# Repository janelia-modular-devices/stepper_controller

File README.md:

# stepper_controller

Authors:

    Peter Polidoro <polidorop@janelia.hhmi.org>

License:

    BSD

## More Detailed Help on Installation and Usage

[modular-devices](https://github.com/janelia-modular-devices/modular-devices)

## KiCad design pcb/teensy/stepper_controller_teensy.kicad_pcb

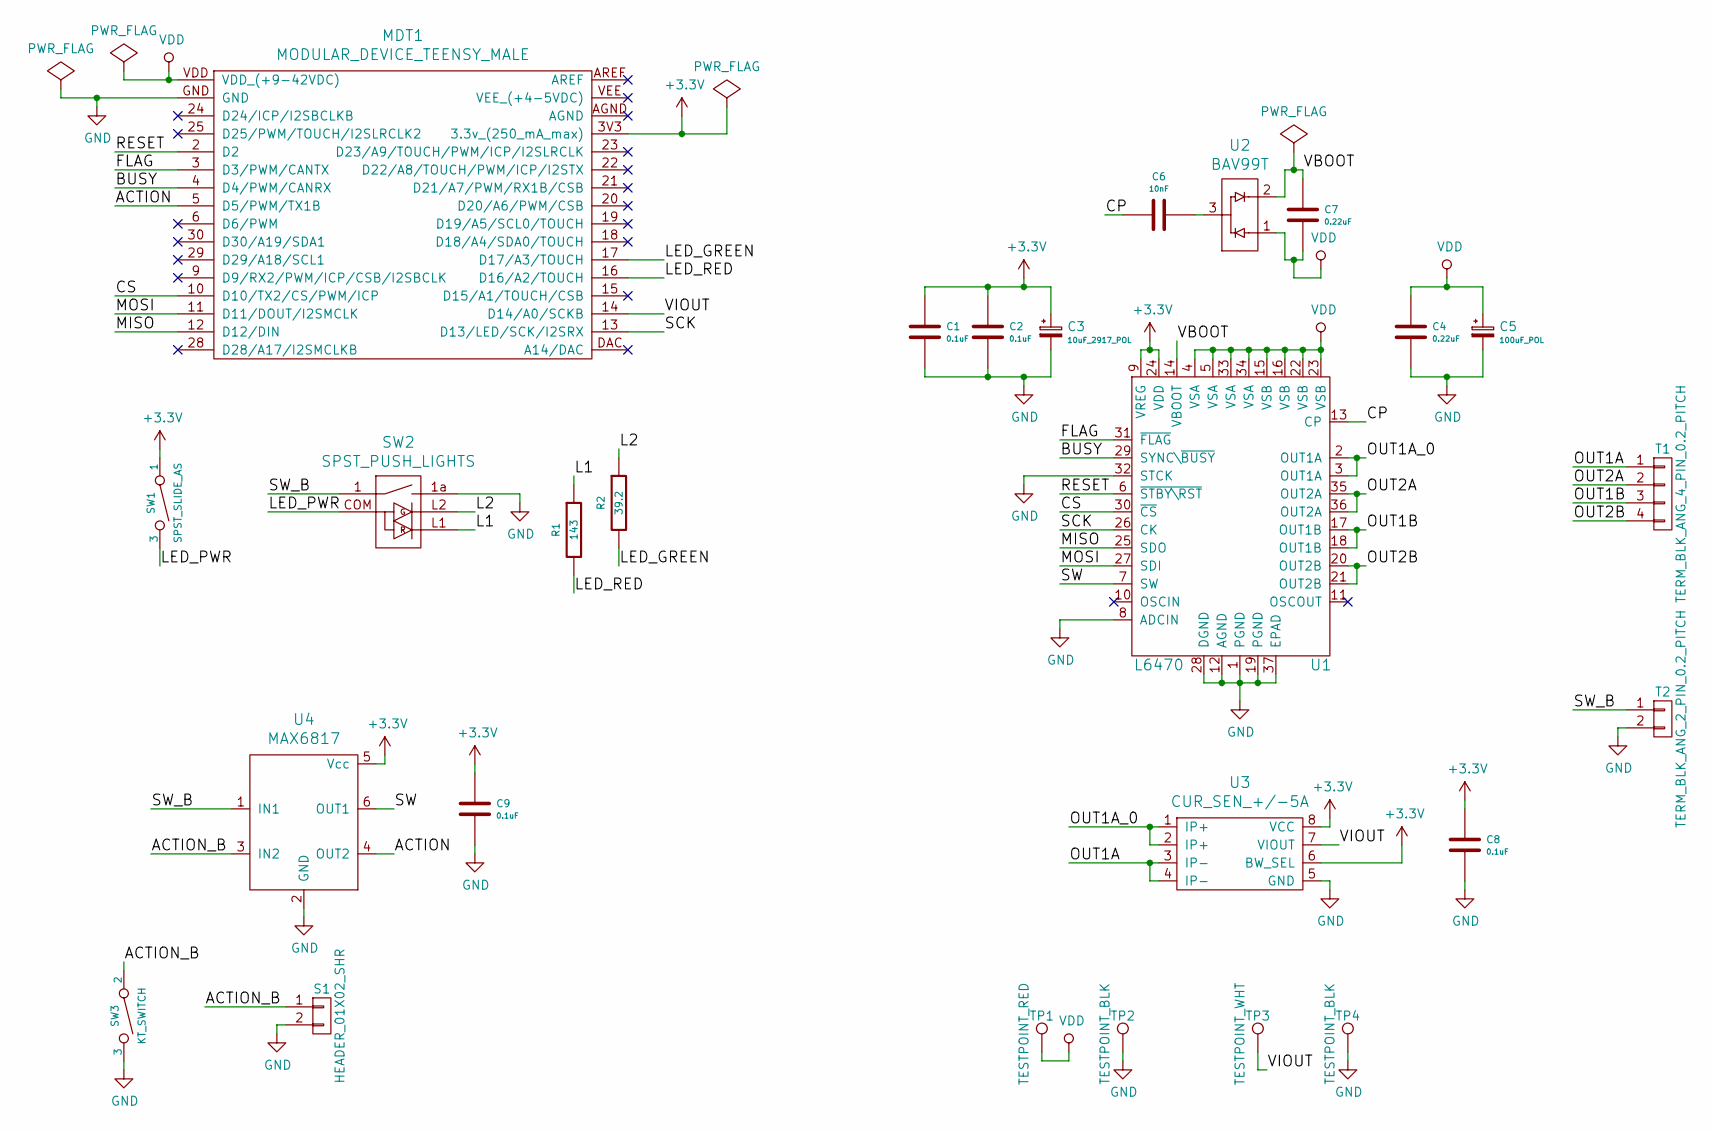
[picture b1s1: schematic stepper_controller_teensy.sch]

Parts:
C1, C2, C8, C9: 0.1uF; SM1210; PartNumber 478-3586-1-ND
C3: 10uF_2917_POL; SM2917_POL; PartNumber 399-8527-1-ND
C4, C7: 0.22uF; SM1210; PartNumber 399-11615-1-ND
C5: 100uF_POL; C_ELEC_12.5; PartNumber 565-2511-1-ND
C6: 10nF; SM1210; PartNumber 399-11960-1-ND
MDT1: MODULAR_DEVICE_TEENSY_MALE; PartNumber S1011E-16-ND
R1: 143; SM1210; PartNumber P143AACT-ND
R2: 39.2; SM1210; PartNumber P39.2AACT-ND
S1: HEADER_01X02_SHR; Header_Shrouded_2_Pin; PartNumber WM4800-ND
SW1: SPST_SLIDE_AS; PartNumber 360-2610-ND
SW2: SPST_PUSH_LIGHTS; KP_SWITCH; PartNumber 360-2461-ND
SW3: KT_SWITCH; PartNumber CKN1860CT-ND
T1: TERM_BLK_ANG_4_PIN_0.2_PITCH; PartNumber A98350-ND
T2: TERM_BLK_ANG_2_PIN_0.2_PITCH; PartNumber A98348-ND
TP1: TESTPOINT_RED; TESTPOINT_THRU; PartNumber 36-5010-ND
TP2, TP4: TESTPOINT_BLK; TESTPOINT_THRU; PartNumber 36-5011-ND
TP3: TESTPOINT_WHT; TESTPOINT_THRU; PartNumber 36-5012-ND
U1: L6470; POWERSO-36; PartNumber 497-16432-1-ND
U2: BAV99T; SOT-523; PartNumber BAV99TCT-ND
U3: CUR_SEN_+/-5A; SOIC_8_LC; PartNumber 620-1634-1-ND
U4: MAX6817; PartNumber MAX6817EUT+TCT-ND

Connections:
+3V3: C1.1, C2.1, C3.1, C8.1, C9.1, MDT1.3V3 (3.3v_(250_mA_max)), SW1.1, U1.9 (VREG), U1.24 (VDD), U3.6 (BW_SEL), U3.8 (VCC), U4.5 (Vcc)
/ACTION: MDT1.5 (D5/PWM/TX1B), U4.4 (OUT2)
/ACTION_B: S1.1, SW3.2, U4.3 (IN2)
/BUSY: MDT1.4 (D4/PWM/CANRX), U1.29 (SYNC\~BUSY)
/CP: C6.1, U1.13 (CP)
/CS: MDT1.10 (D10/TX2/CS/PWM/ICP), U1.30 (~CS)
/FLAG: MDT1.3 (D3/PWM/CANTX), U1.31 (~FLAG)
/L1: R1.1, SW2.L1
/L2: R2.1, SW2.L2
/LED_GREEN: MDT1.17 (D17/A3/TOUCH), R2.2
/LED_PWR: SW1.3, SW2.COM
/LED_RED: MDT1.16 (D16/A2/TOUCH), R1.2
/MISO: MDT1.12 (D12/DIN), U1.25 (SDO)
/MOSI: MDT1.11 (D11/DOUT/I2SMCLK), U1.27 (SDI)
/OUT1A: T1.1, U3.3 (IP-), U3.4 (IP-)
/OUT1A_0: U1.2 (OUT1A), U1.3 (OUT1A), U3.1 (IP+), U3.2 (IP+)
/OUT1B: T1.3, U1.17 (OUT1B), U1.18 (OUT1B)
/OUT2A: T1.2, U1.35 (OUT2A), U1.36 (OUT2A)
/OUT2B: T1.4, U1.20 (OUT2B), U1.21 (OUT2B)
/SCK: MDT1.13 (D13/LED/SCK/I2SRX), U1.26 (CK)
/SW: U1.7 (SW), U4.6 (OUT1)
/SW_B: SW2.1, T2.1, U4.1 (IN1)
/VBOOT: C7.2, U1.14 (VBOOT), U2.2
/VIOUT: MDT1.14 (D14/A0/SCKB), TP3.1, U3.7 (VIOUT)
GND: C1.2, C2.2, C3.2, C4.1, C5.2, C8.2, C9.2, MDT1.GND, S1.2, SW2.1a, SW3.3, T2.2, TP2.1, TP4.1, U1.1 (PGND), U1.8 (ADCIN), U1.12 (AGND), U1.19 (PGND), U1.28 (DGND), U1.32 (STCK), U1.37 (EPAD), U3.5 (GND), U4.2 (GND)
unnamed: C6.2, U2.3
VDD: C4.2, C5.1, C7.1, MDT1.VDD (VDD_(+9-42VDC)), TP1.1, U1.4 (VSA), U1.5 (VSA), U1.15 (VSB), U1.16 (VSB), U1.22 (VSB), U1.23 (VSB), U1.33 (VSA), U1.34 (VSA), U2.1

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
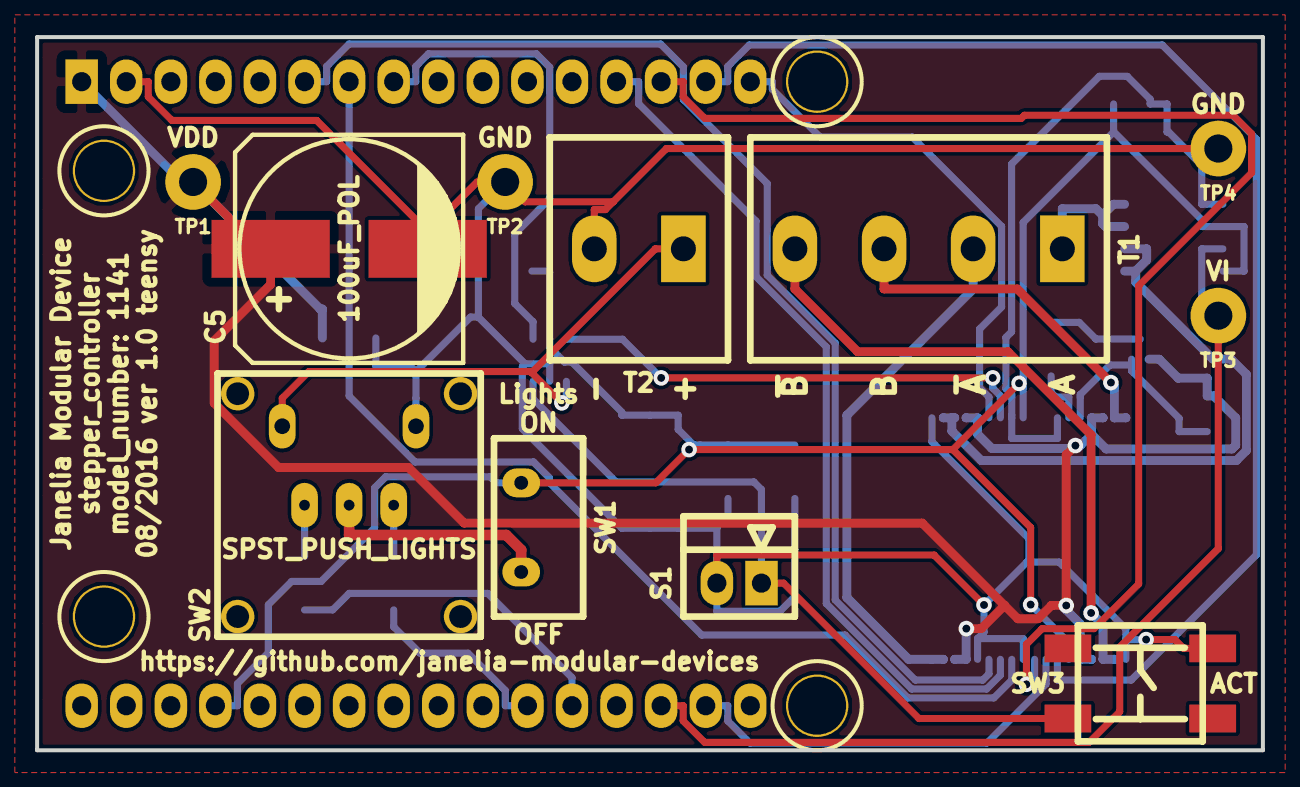
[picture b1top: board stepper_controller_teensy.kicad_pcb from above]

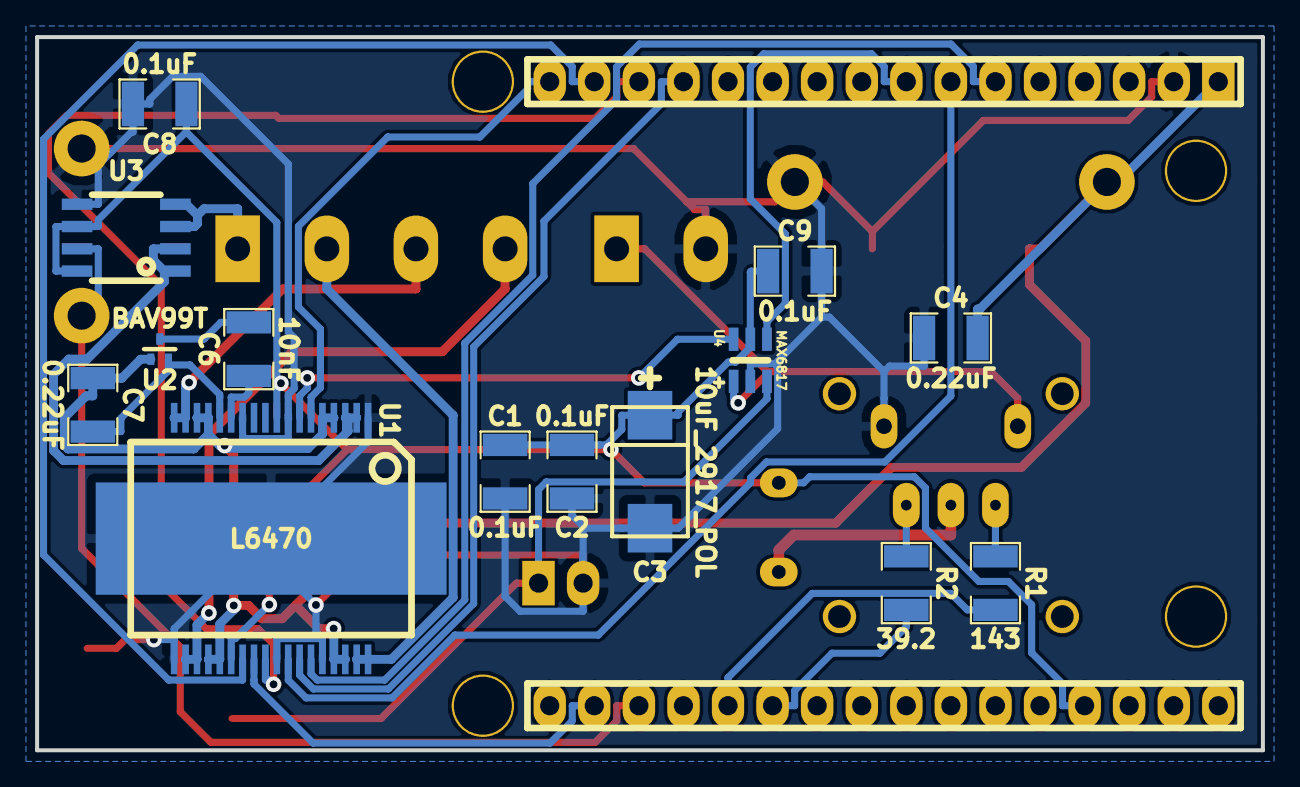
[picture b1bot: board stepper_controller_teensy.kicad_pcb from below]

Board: 2 copper layers, 69.8 x 40.6 mm, 26 parts (14 on the bottom side), 28 nets.

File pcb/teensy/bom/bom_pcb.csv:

Item,Reference(s),Value,Quantity,Description,PartNumber,Vendor
1,C1 C2 C8 C9,0.1uF,4,CAP CER 0.1UF 50V 10% X7R 1210,478-3586-1-ND,digikey
2,C3,10uF_2917_POL,1,CAP TANT 10UF 35V 10% 2917,399-8527-1-ND,digikey
3,C4 C7,0.22uF,2,0.22uF 100V Ceramic Capacitor X7R 1210,399-11615-1-ND,digikey
4,C5,100uF_POL,1,100uF 100V Aluminum Capacitors Radial Can SMD,565-2511-1-ND,digikey
5,C6,10nF,1,10000pF 100V Ceramic Capacitor C0G NP0 1210,399-11960-1-ND,digikey
6,MDT1,MODULAR_DEVICE_TEENSY_MALE,2,16 Position Header Through Hole Male Pins,S1011E-16-ND,digikey
7,R1,143,1,RES SMD 143 OHM 1% 1/2W 1210,P143AACT-ND,digikey
8,R2,39.2,1,RES SMD 39.2 OHM 1% 1/2W 1210,P39.2AACT-ND,digikey
9,S1,HEADER_01X02_SHR,1,CONN HEADER 2POS .100 VERT GOLD,WM4800-ND,digikey
10,SW1,SPST_SLIDE_AS,1,SWITCH SLIDE SPST 0.4VA 28V,360-2610-ND,digikey
11,SW2,SPST_PUSH_LIGHTS,1,Pushbutton Switch SPST-NO Standard Illuminated Through Hole,360-2461-ND,digikey
12,SW3,KT_SWITCH,1,SWITCH TACTILE SPST-NO 1VA 32V,CKN1860CT-ND,digikey
13,T1,TERM_BLK_ANG_4_PIN_0.2_PITCH,1,TERM BLOCK 4POS 35DEG 5.08MM,A98350-ND,digikey
14,T2,TERM_BLK_ANG_2_PIN_0.2_PITCH,1,TERM BLOCK 2POS 35DEG 5.08MM,A98348-ND,digikey
15,U1,L6470,1,Bipolar Motor Driver DMOS SPI PowerSO-36,497-16432-1-ND,digikey
16,U2,BAV99T,1,DIODE DUAL 85V 75MA SOT-523,BAV99TCT-ND,digikey
17,U3,CUR_SEN_+/-5A,1,Current Sensor 5A 1 Channel Hall Effect Open Loop Bidirectional 8-SOIC,620-1634-1-ND,digikey
18,U4,MAX6817,1,IC DEBOUNCER SWITCH DUAL SOT23-6,MAX6817EUT+TCT-ND,digikey

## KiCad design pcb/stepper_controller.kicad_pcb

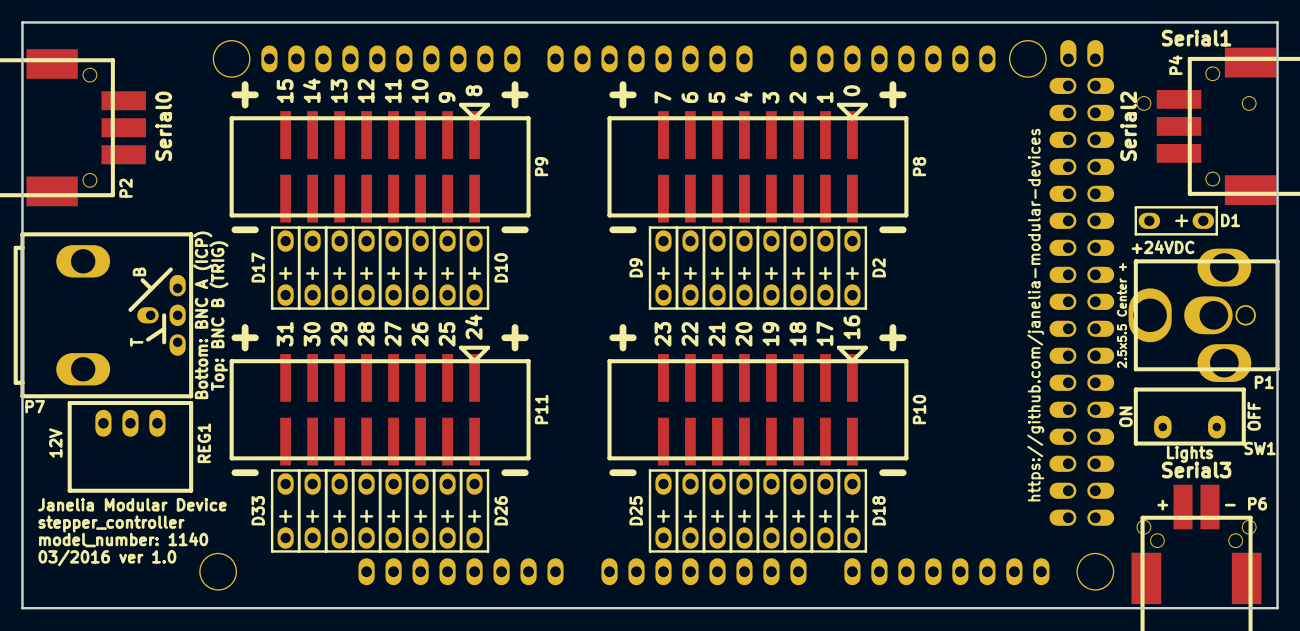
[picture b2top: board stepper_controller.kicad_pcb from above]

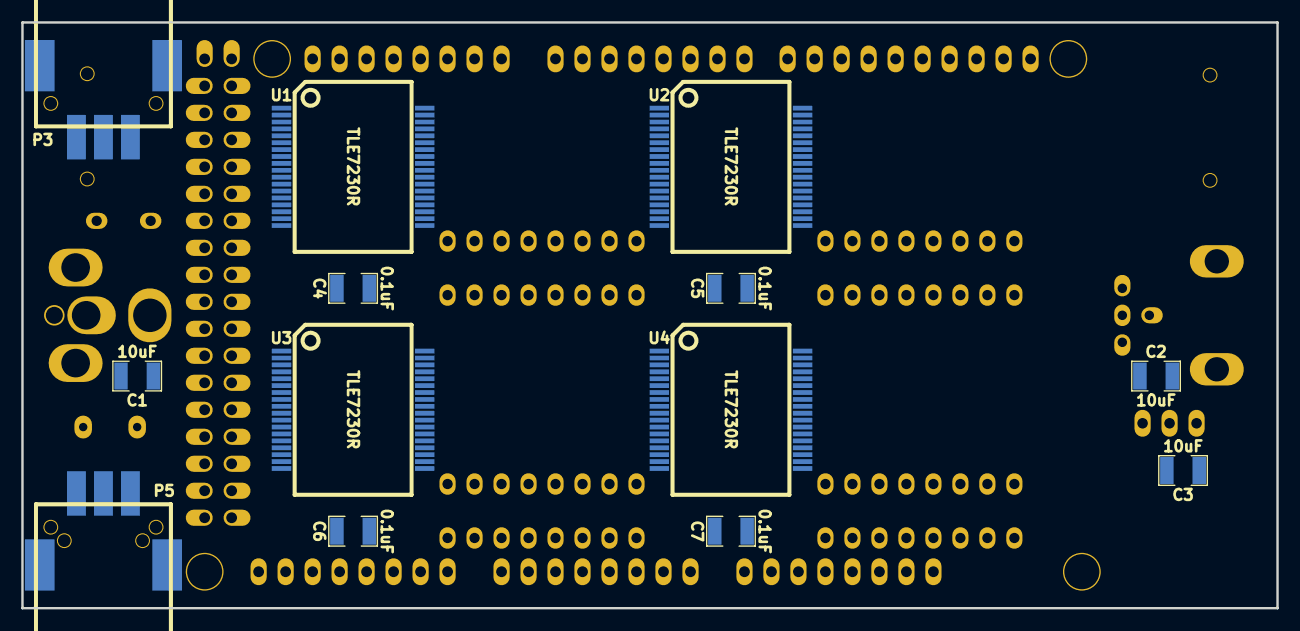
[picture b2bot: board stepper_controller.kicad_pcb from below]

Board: 2 copper layers, 118.1 x 55.1 mm, 58 parts (13 on the bottom side), 55 nets, no tracks yet.

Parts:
ARDUINO1: ARDUINO_MEGA; ARDUINO_MEGA_SHIELD
C1, C2, C3: 10uF; SM1210
C4, C5, C6, C7: 0.1uF; SM1210
D1, D2, D3, D4, D5, D6, D7, D8, D9, D10, D11, D12, D13, D14, D15, D16, D17, D18, D19, D20, D21, D22, D23, D24, D25, D26, D27, D28, D29, D30, D31, D32, D33: LED_24V; LED_555-3XXX
P1: PWR_JACK_2.5x5.5; DCJACK_2PIN_HIGHCURRENT
P2, P3, P4, P5: HEADER_01X03_SMD_RA; Header_3_Pin_SMD_RA
P6: HEADER_01X02_SMD_RA; Header_2_Pin_SMD_RA
P7: BNC_DOUBLE_RA; BNC_DOUBLE
P8, P9, P10, P11: HEADER_02X08_SMD; HEADER_02x08_SMD
REG1: CONV_DC_DC_12V_1A; DC_DC_CONV_R78C
SW1: SPST_SLIDE_AS
U1, U2, U3, U4: TLE7230R; PG-DSO-36

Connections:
+5V: ARDUINO1.5V_1, C4.1, C5.1, C6.1, C7.1, U1.8, U1.25, U2.8, U2.25, U3.8, U3.25, U4.8, U4.25
/BNC_A: ARDUINO1.48, P7.1
/BNC_B: ARDUINO1.3, P7.3
/CS: ARDUINO1.46, U1.10, U2.10, U3.10, U4.10
/LED_PWR: D1.1, D2.1, D3.1, D4.1, D5.1, D6.1, D7.1, D8.1, D9.1, D10.1, D11.1, D12.1, D13.1, D14.1, D15.1, D16.1, D17.1, D18.1, D19.1, D20.1, D21.1, D22.1, D23.1, D24.1, D25.1, D26.1, D27.1, D28.1, D29.1, D30.1, D31.1, D32.1, D33.1, SW1.3
/MISO: ARDUINO1.50, U4.27
/MOSI: ARDUINO1.51, U1.29
/OUT0: D2.2, P8.2, U1.4
/OUT1: D3.2, P8.4, U1.5
/OUT2: D4.2, P8.6, U1.14
/OUT3: D5.2, P8.8, U1.15
/OUT4: D6.2, P8.10, U1.22
/OUT5: D7.2, P8.12, U1.23
/OUT6: D8.2, P8.14, U1.32
/OUT7: D9.2, P8.16, U1.33
/OUT8: D10.2, P9.2, U2.4
/OUT9: D11.2, P9.4, U2.5
/OUT10: D12.2, P9.6, U2.14
/OUT11: D13.2, P9.8, U2.15
/OUT12: D14.2, P9.10, U2.22
/OUT13: D15.2, P9.12, U2.23
/OUT14: D16.2, P9.14, U2.32
/OUT15: D17.2, P9.16, U2.33
/OUT16: D18.2, P10.2, U3.4
/OUT17: D19.2, P10.4, U3.5
/OUT18: D20.2, P10.6, U3.14
/OUT19: D21.2, P10.8, U3.15
/OUT20: D22.2, P10.10, U3.22
/OUT21: D23.2, P10.12, U3.23
/OUT22: D24.2, P10.14, U3.32
/OUT23: D25.2, P10.16, U3.33
/OUT24: D26.2, P11.2, U4.4
/OUT25: D27.2, P11.4, U4.5
/OUT26: D28.2, P11.6, U4.14
/OUT27: D29.2, P11.8, U4.15
/OUT28: D30.2, P11.10, U4.22
/OUT29: D31.2, P11.12, U4.23
/OUT30: D32.2, P11.14, U4.32
/OUT31: D33.2, P11.16, U4.33
/RESET: ARDUINO1.44, U1.9, U2.9, U3.9, U4.9
/RX0: ARDUINO1.0, P2.1
/RX1: ARDUINO1.19, P3.1
/RX2: ARDUINO1.17, P4.1
/RX3: ARDUINO1.15, P5.1
/SCK: ARDUINO1.52, U1.28, U2.28, U3.28, U4.28
/SO1: U1.27, U2.29
/SO2: U2.27, U3.29
/SO3: U3.27, U4.29
/TX0: ARDUINO1.1, P2.3
/TX1: ARDUINO1.18, P3.3
/TX2: ARDUINO1.16, P4.3
/TX3: ARDUINO1.14, P5.3
/V_IN: ARDUINO1.V_IN, C3.1, REG1.3
GND: ARDUINO1.GND1, ARDUINO1.GND2, C1.2, C2.2, C3.2, C4.2, C5.2, C6.2, C7.2, D1.2, P1.2, P2.2, P3.2, P4.2, P5.2, P6.1, P7.2, P7.4, REG1.2, U1.1, U1.6, U1.7, U1.12, U1.13, U1.18, U1.19, U1.36, U2.1, U2.6, U2.7, U2.12, U2.13, U2.18, U2.19, U2.36, U3.1, U3.6, U3.7, U3.12, U3.13, U3.18, U3.19, U3.36, U4.1, U4.6, U4.7, U4.12, U4.13, U4.18, U4.19, U4.36
VAA: C1.1, C2.1, P1.1, P6.2, P8.1, P8.3, P8.5, P8.7, P8.9, P8.11, P8.13, P8.15, P9.1, P9.3, P9.5, P9.7, P9.9, P9.11, P9.13, P9.15, P10.1, P10.3, P10.5, P10.7, P10.9, P10.11, P10.13, P10.15, P11.1, P11.3, P11.5, P11.7, P11.9, P11.11, P11.13, P11.15, REG1.1, SW1.1

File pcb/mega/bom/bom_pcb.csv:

Item,Reference(s),Value,Quantity,Description,PartNumber,Vendor
1,ARDUINO1,ARDUINO_MEGA,1,BOARD MCU MEGA2560,1050-1018-ND,digikey
2,C1 C2 C3,10uF,3,CAP CER 10UF 50V 10% X7S 1210,445-4536-1-ND,digikey
3,C4 C5 C6 C7,0.1uF,4,CAP CER 0.1UF 50V 10% X7R 1210,478-3586-1-ND,digikey
4,D1 D10 D11 D12 D13 D14 D15 D16 D17 D18 D19 D2 D20 D21 D22 D23 D24 D25 D26 D27 D28 D29 D3 D30 D31 D32 D33 D4 D5 D6 D7 D8 D9,LED_24V,33,LED 2MM 24V VERTICAL RED PC MNT,350-1723-ND,digikey
5,P1,PWR_JACK_2.5x5.5,1,CONN PWR JACK DC 2.5X5.5 8A T/H,CP-063BH-ND,digikey
6,P10 P11 P8 P9,HEADER_02X08_SMD,4,CONN HEADR 2.54MM 16POS GOLD SMD,S9187-ND,digikey
7,P2 P3 P4 P5,HEADER_01X03_SMD_RA,4,CONN HEADER 3POS R/A SMD GOLD,A100890CT-ND,digikey
8,P6,HEADER_01X02_SMD_RA,1,CONN HEADER 2POS R/A SMD GOLD,A100903CT-ND,digikey
9,P7,BNC_DOUBLE_RA,1,CONN BNC JACK R/A 75 OHM PCB,ACX1655-ND,digikey
10,REG1,CONV_DC_DC_12V_1A,1,CONV DC/DC 1A 12V OUT SIP VERT,945-1392-5-ND,digikey
11,SW1,SPST_SLIDE_AS,1,SWITCH SLIDE SPST 0.4VA 28V,360-2610-ND,digikey
12,U1 U2 U3 U4,TLE7230R,4,IC SW SMART OCTAL LOWSIDE PDSO36,TLE7230RCT-ND,digikey

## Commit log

2015-07-24 Initial commit.
2015-07-24 Added initial pcb files.
2015-07-24 Added enclosure and image files.
2015-07-24 Updated documentation.
2015-07-24 Initial commit of firmware files.
2015-07-24 Added initial stepper files.
2015-07-24 Added intial MotorDrive files.
2015-07-24 Updated Stepper to new firmware style.
2015-07-24 Updated MotorDrive to new firmware style.
2015-07-24 <TimerOne.h> -> "TimerOne.h".
2015-07-24 Progress towards getting firmware to work with the new style.
2015-07-27 Added basic functionality.
2015-07-27 Progress towards getting tone to work.
2015-07-27 Added tone methods.
2015-07-28 boolean -> bool.
2015-07-28 Added waypoint repeat methods.
2015-07-29 interrupt -> switch_interrupt.
2015-07-29 Separated switch and bnc interrupts.
2015-07-29 getStatus -> getControllerInfo.
2016-02-16 Major changes to prepare for pcb mounted stepper driver.
2016-03-07 Use power_switch_controller as base for pcb.
2016-03-07 Progress towards pcb 1.0.
2016-03-07 Added IM483H to schematic.
2016-03-09 Progress towards firmware update.
2016-03-09 Progress towards compiling.
2016-03-10 Updated firmware.
2016-08-09 Created stepper_controller_mega.
2016-08-09 footprints: -> stepper_controller_mega:.
2016-08-09 Added stepper_controller_teensy.
2016-08-09 Added L6470.
2016-08-09 Added TERM_BLK_ANG_4_PIN.
2016-08-09 Added terminal blocks.
2016-08-10 Added components and footprints.
2016-08-10 Added resistors.
2016-08-11 Progress towards teensy pcb v1.0.
2016-08-17 Added components.
2016-08-19 Added component and made changes.
2016-08-24 Progress towards pcb v1.0.
2016-08-24 Adjusted footprints.
2016-08-24 Finished teensy pcb v1.0.
2016-08-31 Updated bom to include testpoints.
2016-08-31 Order testpoints.
2016-09-19 Updated spaces around pointers and references.
2016-09-21 pcb -> hardware.
2017-05-15 Removed stepper_controller firmware.
2017-05-15 Added firmware/StepperController.
2017-08-24 Removed old hardware files.
2017-08-24 Added hardware submodules.
2018-04-12 Updated submodules.
2018-04-12 *.md -> *.org.
2018-05-18 Submodule update.
2018-08-12 polidorop@janelia.hhmi.org -> peterpolidoro@gmail.com
2018-08-27 Combined software and hardware licenses.
2021-09-17 Update email address
